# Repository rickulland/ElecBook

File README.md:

Here is (soon) a recreation of the old Radio Shack Electronic book, reduced to um, 8.5/11ths size? The 'booklet' print size that fits 2 full pages side by side on one sheet and often involves a staple. Don't build this just yet, we are checking resistor things because Ken is a troublemaker. See: Canadien Retrothings on the yew 2be.
 
## CBOARD directory ##
   the KiCAD 7 project to create the switch board. File list needs a haircut, also CoNect will have these boards for cheap soon. 

## OVERSHEET directory ##
   the FreeCAD 1.0 project to make the 'trampoline' keypads. If you just want to print one, ELECbook3.stl should be sliceable by most anything. 

## COVER SHEET (RSN) ##
   print this on the heaviest paper your printer allows, or add a liner sheet to double it up. Fold in half, print side out.

## PAGE PROTECTOR ##
   'inside load' sheet protector pouch for half sized (booklet sized) 3 hole binders

## ASSEMBLY ##
   stack the 3D printed oversheet (flat side up) over the completed circuit board - key 1 is top left. thin 2sided tape optional.
   Slip inside the folded cover sheet, fold outside 
   all this inside the plastic page protector.

More soon 
-ricku

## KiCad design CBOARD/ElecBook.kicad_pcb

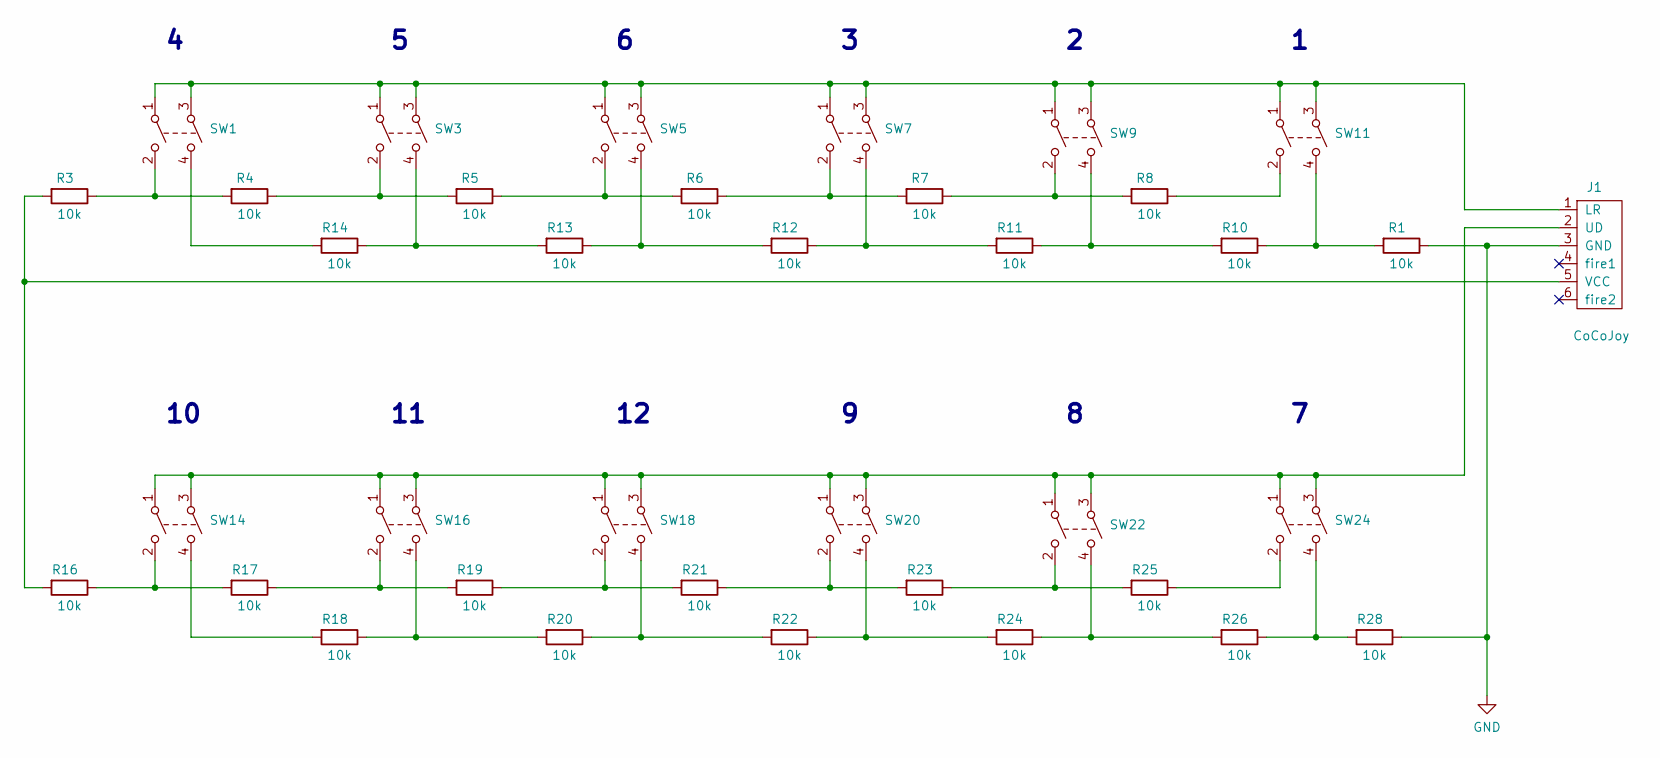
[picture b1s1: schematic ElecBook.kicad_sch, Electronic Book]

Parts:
J1: CoCoJoy; PinHeader_1x05_P2.00mm_Vertical
R1, R3, R4, R5, R6, R7, R8, R10, R11, R12, R13, R14, R16, R17, R18, R19, R20, R21, R22, R23, R24, R25, R26, R28: 10k; R_Axial_DIN0207_L6.3mm_D2.5mm_P7.62mm_Horizontal
SW1, SW3, SW5, SW7, SW9, SW11, SW14, SW16, SW18, SW20, SW22, SW24: SW_DPST; SW_PUSH1_6mm_H4.3mm

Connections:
GND: J1.3 (GND), R1.1, R28.1; also elsewhere on the board
unnamed: J1.1 (LR), SW1.1, SW1.3, SW3.1, SW3.3, SW5.1, SW5.3, SW7.1, SW7.3, SW9.1, SW9.3, SW11.1, SW11.3
unnamed: J1.2 (UD), SW14.1, SW14.3, SW16.1, SW16.3, SW18.1, SW18.3, SW20.1, SW20.3, SW22.1, SW22.3, SW24.1, SW24.3
unnamed: J1.5 (VCC), R3.2, R16.2
unnamed: R3.1, R4.2, SW1.2
unnamed: R4.1, R5.2, SW3.2
unnamed: R5.1, R6.2, SW5.2
unnamed: R6.1, R7.2, SW7.2
unnamed: R7.1, R8.2, SW9.2
unnamed: R8.1, SW11.2
unnamed 10: R1.2, R10.1, SW11.4; also elsewhere on the board
unnamed: R10.2, R11.1, SW9.4
unnamed: R11.2, R12.1, SW7.4
unnamed: R12.2, R13.1, SW5.4
unnamed: R13.2, R14.1, SW3.4
unnamed: R14.2, SW1.4
unnamed: R16.1, R17.2, SW14.2
unnamed: R17.1, R19.2, SW16.2
unnamed: R18.1, R20.2, SW16.4
unnamed: R18.2, SW14.4
unnamed: R19.1, R21.2, SW18.2
unnamed: R20.1, R22.2, SW18.4
unnamed: R21.1, R23.2, SW20.2
unnamed: R22.1, R24.2, SW20.4
unnamed: R23.1, R25.2, SW22.2
unnamed: R24.1, R26.2, SW22.4
unnamed: R25.1, SW24.2
unnamed: R26.1, R28.2, SW24.4

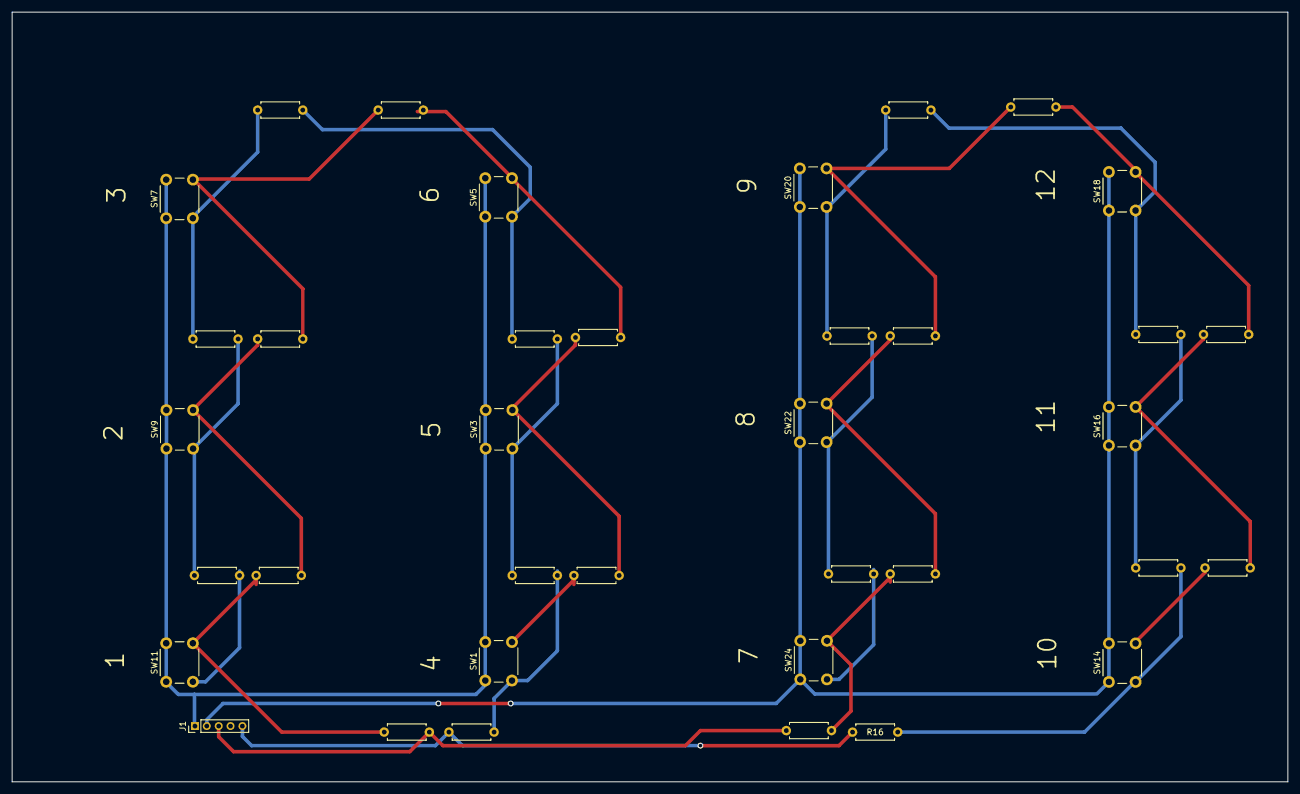
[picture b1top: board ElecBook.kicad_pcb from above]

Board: 2 copper layers, 215.1 x 129.8 mm, 37 parts (0 on the bottom side), 28 nets.

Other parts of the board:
R9: 10k; R_Axial_DIN0207_L6.3mm_D2.5mm_P7.62mm_Horizontal

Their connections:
GND: R9.1; also elsewhere on the board
unnamed 10: R9.2; also elsewhere on the board

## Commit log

2025-09-27 first
2025-09-27 already a reorg
